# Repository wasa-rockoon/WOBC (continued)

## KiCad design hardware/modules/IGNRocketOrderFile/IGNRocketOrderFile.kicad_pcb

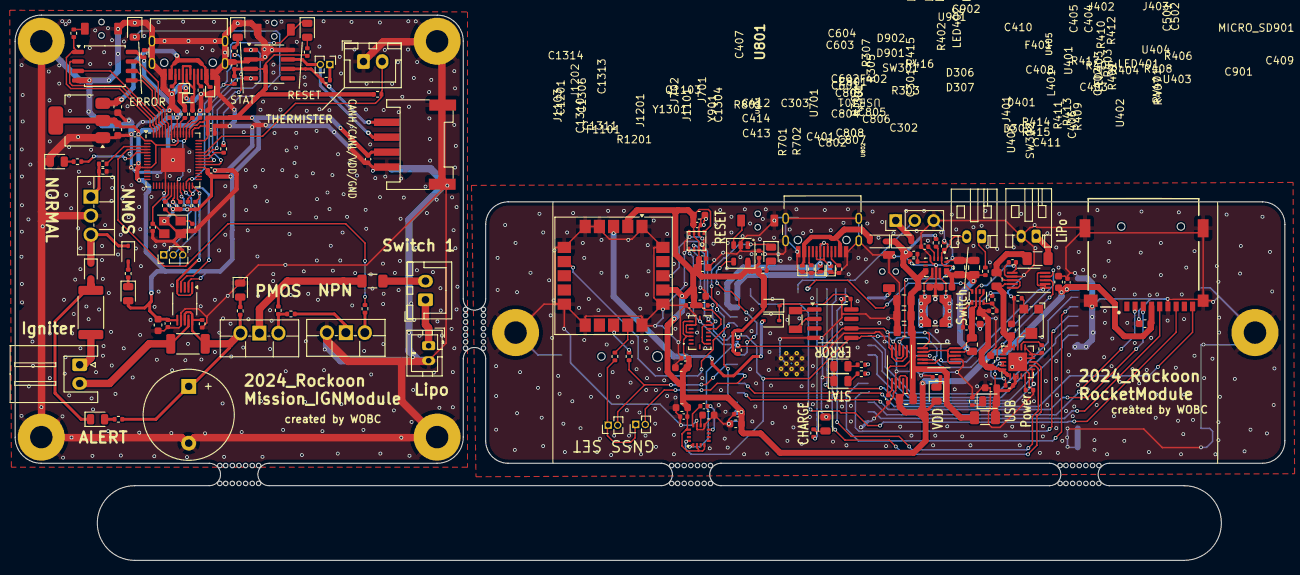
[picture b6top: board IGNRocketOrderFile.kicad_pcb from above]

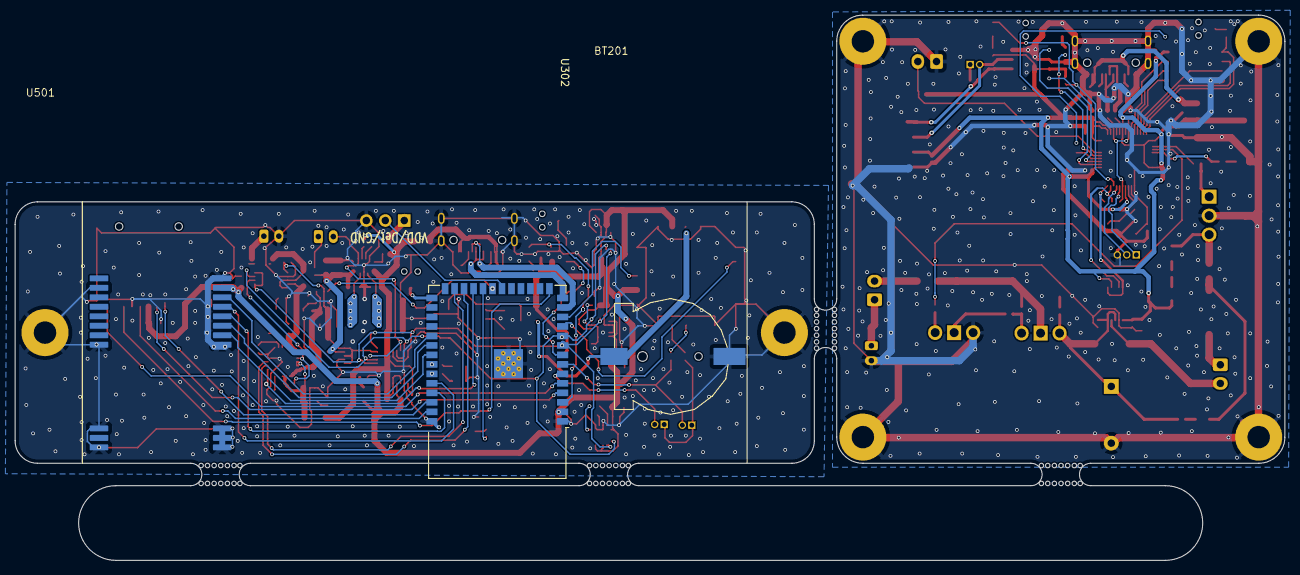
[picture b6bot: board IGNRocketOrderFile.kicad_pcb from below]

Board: 2 copper layers, 170.0 x 73.0 mm, 182 parts (3 on the bottom side), 126 nets.

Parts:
BT201: Battery_Cell; cr1220
BZ1101: Buzzer; Buzzer_12x9.5RM7.6
C301, C303, C403, C409, C410, C415, C502, C602, C603, C801, C802, C807, C902, C1102, C1201, C1301, C1302, C1305, C1306, C1308, C1310, C1311, C1312, C1313, C1314, C1315: 100nF; C_0402_1005Metric
C302, C401, C402, C406, C407, C408, C411, C501, C601, C604, C803, C804, C808, C901, C1001, C1002, C1101: 10uF; C_0603_1608Metric
C404, C405, C412, C413, C414: 22uF; C_0805_2012Metric
C805: 0.22uF; C_0402_1005Metric
C806: 4.7uF; C_0603_1608Metric
C1303, C1304: 27pF; C_0402_1005Metric
C1307, C1309: 1uF; C_0402_1005Metric
D301, D302, D304, D1302, D1303, D1304: 5V; D_SOD-882D
D303, D401, D901, D902: D; D_SOD-323
D305, D1301: RESET; LED_0805_2012Metric
D306, D1306: ERROR; LED_0805_2012Metric
D307, D1305: STAT; LED_0805_2012Metric
D1101: PMOS; LED_0805_2012Metric
D1102, D1104: D_Schottky; D_SOD-323
D1103: ALERT; LED_0805_2012Metric
D1105: NMOS; LED_0805_2012Metric
D1106: NORMAL; LED_0805_2012Metric
F401, F402, F1101: Polyfuse; Fuse_1206_3216Metric
J401: Conn_01x03; PinHeader_1x03_P2.54mm_Vertical
J402: Ext Switch; JST_PH_S2B-PH-K_1x02_P2.00mm_Horizontal
J403: LiPo; JST_PH_S2B-PH-K_1x02_P2.00mm_Horizontal
J701, J702: Conn_01x02; PinHeader_1x02_P1.27mm_Vertical
J1001: THERMISTER; JST_XH_B2B-XH-A_1x02_P2.50mm_Vertical
J1101: LiPo 1 Cell; JST_PH_B2B-PH-K_1x02_P2.00mm_Vertical
J1102: IGNITER; JST_XH_S2B-XH-A_1x02_P2.50mm_Horizontal
J1103: PowerSW; JST_XH_B2B-XH-A_1x02_P2.50mm_Vertical
J1201: Jumper; PinHeader_1x02_P1.27mm_Vertical
J1202: Conn_01x04_MountingPin; Grove_4P_L_SMD
J1301: DEBUG; PinHeader_1x03_P1.27mm_Vertical
L401: L; L_Wuerth_WE-TPC-3816
LED401: USB Power; LED_0805_2012Metric
LED402: CHARGE; LED_0805_2012Metric
LED403: VDD; LED_0805_2012Metric
MICRO_SD901: TF-01A
Q1101: Q_PMOS_GSD; TO-220F-3_Vertical
Q1102: Q_NMOS_GSD; TO-220F-3_Vertical
Q1103: Q_NPN_BEC; TO-220F-3_Vertical
R301, R302, R1303, R1304: 5.1k; R_0402_1005Metric
R303, R304, R306, R701, R702: 470; R_0402_1005Metric
R305, R307, R405, R406, R410, R1001, R1102, R1105, R1106, R1301, R1309, R1311: 10k; R_0402_1005Metric
R401, R402, R404, R417, R1101, R1108, R1110, R1111, R1112, R1302, R1305, R1308, R1310, R1312: 1k; R_0402_1005Metric
R403, R801: 4.7k; R_0402_1005Metric
R407, R408, R413: 100k; R_0402_1005Metric
R409, R412, R416: 50mΩ; R_0805_2012Metric
R411: 330k; R_0402_1005Metric
R414: 15k; R_0402_1005Metric
R415: 47k; R_0402_1005Metric
R1103: 20mΩ; R_2010_5025Metric
R1104: 1; R_2512_6332Metric
R1107, R1109: 510; R_0402_1005Metric
R1201: 120; R_0402_1005Metric
R1306, R1307: 22.4; R_0402_1005Metric
RV401: RV10k; Potentiometer_Bourns_TC33X_Vertical
SW301, SW1301: RESET_sw; TVAF06-A020B-R
SW302: Boot_sw; TVAF06-A020B-R
SW1302: BOOT0; TVAF06-A020B-R
U301: TPS3820; SOT-23-5
U302: ESP32-S3-WROOM-1
U401: TPS2116DRL; SOT-583-8
U402: MCP73871-1CC; QFN-20-1EP_4x4mm_P0.5mm_EP2.5x2.5mm
U403, U404, U406, U1101: INA226; VSSOP-10_3x3mm_P0.5mm
U405: TPS63070RNMR; VREG_TPS63070RNMR
U501: E220-900T22S(JP)
U601: BME280
U701: SAM-M10Q; ublox_SAM-M8Q
U801: BMI088
U802: QMC5883L; _HMC5883L
U901: PCF8563T; SOIC-8_3.9x4.9mm_P1.27mm
U1001: AMS1117-3.3; SOT-223-3_TabPin2
U1301: SN65HVD230; SOIC-8_3.9x4.9mm_P1.27mm
U1302: W25Q128JVS; SOIC-8_5.23x5.23mm_P1.27mm
U1303: RP2040; QFN-56-1EP_7x7mm_P0.4mm_EP3.2x3.2mm
USB301, USB1301: USB_C_Receptacle_USB2.0; USB_C_TYPEC-301S-ACP16X7
Y901: Crystal; Crystal_SMD_3215-2Pin_3.2x1.5mm
Y1301: Crystal_GND24; Crystal_SMD_3225-4Pin_3.2x2.5mm

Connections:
+BATT: BT201.1 (+), D901.2 (A), U701.3 (V_BCKP)
/IGN/HIGH: R1111.1, U1303.4 (GPIO2)
/IGN/I2C_SCL: R1311.2, U1101.1 (A1), U1101.5 (SCL), U1303.28 (GPIO17)
/IGN/I2C_SDA: R1309.2, U1101.4 (SDA), U1303.27 (GPIO16)
/IGN/IF/CANH: J1202.1, R1201.2, U1301.6 (CANL)
/IGN/IF/CANL: J1201.2, J1202.2, U1301.7 (CANH)
/IGN/LOW: R1109.1, U1303.3 (GPIO1)
/IGN/Normal: R1112.1, U1303.5 (GPIO3)
/IGN/RP2040core/CAN_RX: U1301.4 (R), U1303.35 (GPIO23)
/IGN/RP2040core/CAN_TX: U1301.1 (D), U1303.34 (GPIO22)
/IGN/RP2040core/GPIO26_ADC0: J1001.2, R1001.2, U1303.38 (GPIO26_ADC0)
/IGN/RP2040core/USB_D+: D1303.2 (A2), R1306.1, USB1301.A6 (D+), USB1301.B6 (D+)
/IGN/RP2040core/USB_D-: D1304.2 (A2), R1307.1, USB1301.A7 (D-), USB1301.B7 (D-)
/Rocket/AUX: U302.31 (GPIO38/FSPIWP/SUBSPIWP), U501.9 (AUX)
/Rocket/CHARGE: R402.2, U302.22 (GPIO14/TOUCH14/ADC2_CH3/FSPIWP/FSPIDQS/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)
/Rocket/CLK: MICRO_SD901.5 (CLK), U302.39 (GPIO1/TOUCH1/ADC1_CH0)
/Rocket/DetL: J401.2, U302.20 (GPIO12/TOUCH12/ADC2_CH1/FSPICLK/FSPIIO6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)
/Rocket/ESP32Core2/USB_D+: D302.2 (A2), U302.14 (GPIO20/U1CTS/ADC2_CH9/CLK_OUT1/USB_D+), USB301.A6 (D+), USB301.B6 (D+)
/Rocket/ESP32Core2/USB_D-: D304.2 (A2), U302.13 (GPIO19/U1RTS/ADC2_CH8/CLK_OUT2/USB_D-), USB301.A7 (D-), USB301.B7 (D-)
/Rocket/ESP32Core2/WDI: U301.4 (WDI), U302.8 (GPIO15/U0RTS/ADC2_CH4/XTAL_32K_P)
/Rocket/GPS_RESET: U302.12 (GPIO8/TOUCH8/ADC1_CH7/SUBSPICS1), U701.18 (~RESET)
/Rocket/I2C_SCL: R305.2, U302.9 (GPIO16/U0CTS/ADC2_CH5/XTAL_32K_N), U403.1 (A1), U403.5 (SCL), U404.1 (A1), U404.2 (A0), U404.5 (SCL), U406.1 (A1), U406.5 (SCL), U601.4 (SCK), U801.8 (SCL/SCK), U802.1 (SCL), U901.6 (SCL)
/Rocket/I2C_SDA: R307.2, U302.10 (GPIO17/U1TXD/ADC2_CH6), U403.4 (SDA), U404.4 (SDA), U406.2 (A0), U406.4 (SDA), U601.3 (SDI), U801.9 (SDA/SDI), U802.16 (SDA), U901.5 (SDA)
/Rocket/LiPoPower2/PROG: RV401.2, U402.13 (PROG1)
/Rocket/M0: U302.33 (MTDO/GPIO40/CLK_OUT2), U501.5 (M0)
/Rocket/M1: U302.32 (MTCK/GPIO39/CLK_OUT3/SUBSPICS1), U501.6 (M1)
/Rocket/MISO: MICRO_SD901.7 (DAT0), U302.15 (GPIO3/TOUCH3/ADC1_CH2)
/Rocket/MOSI: MICRO_SD901.3 (CMD), U302.4 (GPIO4/TOUCH4/ADC1_CH3)
/Rocket/PG: U302.23 (GPIO21), U402.6 (~PG)
/Rocket/RTX0: U302.36 (U0RXD/GPIO44/CLK_OUT2), U501.8 (TXD)
/Rocket/RTX1: J702.2, R702.2, U302.7 (GPIO7/TOUCH7/ADC1_CH6)
/Rocket/SD_DET: MICRO_SD901.CD1 (CD), U302.5 (GPIO5/TOUCH5/ADC1_CH4)
/Rocket/SS: MICRO_SD901.2 (CD/DAT3), U302.38 (GPIO2/TOUCH2/ADC1_CH1)
/Rocket/ST: U302.21 (GPIO13/TOUCH13/ADC2_CH2/FSPIQ/FSPIIO7/S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), U401.8 (ST)
/Rocket/STAT1: U302.24 (GPIO47/SPICLK_P/SUBSPICLK_P_DIFF), U402.8 (STAT1/~LBO)
/Rocket/STAT2: U302.25 (GPIO48/SPICLK_N/SUBSPICLK_N_DIFF), U402.7 (STAT2)
/Rocket/TRX0: U302.37 (U0TXD/GPIO43/CLK_OUT1), U501.7 (RXD)
/Rocket/TRX1: J701.2, U302.6 (GPIO6/TOUCH6/ADC1_CH5)
/Rocket/TimePulse: U302.11 (GPIO18/U1RXD/ADC2_CH7/CLK_OUT3), U701.7 (TIMEPULSE)
GND: BT201.2 (-), BZ1101.2 (-), C301.1, C302.1, C303.2, C401.2, C402.2, C403.2, C404.2, C405.2, C406.2, C407.2, C408.2, C409.2, C410.2, C411.2, C412.2, C413.2, C414.2, C415.2, C501.2, C502.2, C601.2, C602.2, C603.2, C604.2, C801.2, C802.2, C803.2, C804.2, C806.2, C807.2, C808.2, C901.2, C902.1, C1001.2, C1002.2, C1101.2, C1102.2, C1201.1, C1301.1, C1302.1, C1303.1, C1304.1, C1305.2, C1306.2, C1307.1, C1308.2, C1309.1, C1310.2, C1311.2, C1312.2, C1313.2, C1314.2, C1315.2, D301.1 (A1), D302.1 (A1), D304.1 (A1), D306.1 (K), D307.1 (K), D1101.1 (K), D1106.1 (K), D1302.1 (A1), D1303.1 (A1), D1304.1 (A1), D1305.1 (K), D1306.1 (K), J401.3, J403.2, J1001.1, J1101.2, J1202.4, J1202.MP (MountPin), J1301.3, LED402.1 (K), MICRO_SD901.6 (VSS), MICRO_SD901.MP1 (SHIELD), MICRO_SD901.MP2 (SHIELD), MICRO_SD901.MP3 (SHIELD), MICRO_SD901.MP4 (SHIELD), Q1102.3 (D), Q1103.3 (E), R301.2, R302.2, R401.2, R403.1, R404.2, R406.2, R407.2, R411.2, R414.1, R417.2, R1102.1, R1106.1, R1303.2, R1304.2, SW301.2, SW302.2, SW1301.2, SW1302.1, U301.2 (GND), U302.1 (GND), U302.40 (GND), U302.41 (GND), U401.1 (GND), U402.9 (~TE), U402.10 (V_{SS}), U402.11 (V_{SS}), U402.21 (V_{SS}), U403.7 (GND), U404.7 (GND), U405.4 (GND), U405.10 (PGND), U405.15 (VSEL), U406.7 (GND), U501.1 (GND), U501.2 (GND), U501.3 (GND), U501.4 (GND), U501.11 (GND), U501.13 (GND), U501.19 (GND), U501.20 (GND), U501.22 (GND), U601.1 (GND), U601.5 (SDO), U601.7 (GND), U701.1 (GND), U701.4 (GND), U701.5 (GND), U701.6 (GND), U701.10 (GND), U701.11 (GND), U701.15 (GND), U701.16 (GND), U701.20 (GND), U801.4 (GNDA), U801.6 (GNDIO), U802.9 (GND), U802.11 (GND), U901.4 (VSS), U1001.1 (GND), U1101.7 (GND), U1301.2 (GND), U1301.8 (Rs), U1302.4 (GND), U1303.19 (TESTEN), U1303.57 (GND), USB301.A1 (GND), USB301.A12 (GND), USB301.B1 (GND), USB301.B12 (GND), USB301.S1 (SHIELD), USB1301.A1 (GND), USB1301.A12 (GND), USB1301.B1 (GND), USB1301.B12 (GND), USB1301.S1 (SHIELD), Y1301.2, Y1301.4
unnamed: BZ1101.1 (+), Q1101.3 (S), R1101.1, R1102.2, R1103.2, R1108.1, U1101.8 (Vbus), U1101.10 (Vin+)
unnamed: C1304.2, R1308.1, Y1301.1
unnamed: D301.2 (A2), D303.2 (A), USB301.A4 (VBUS), USB301.A9 (VBUS), USB301.B4 (VBUS), USB301.B9 (VBUS)
unnamed: D305.2 (A), R303.2
unnamed: D306.2 (A), R304.2
unnamed: D307.2 (A), R306.2
unnamed: D401.2 (A), J401.1
unnamed: C902.2, D901.1 (K), D902.1 (K), U901.8 (VDD)
unnamed: D1101.2 (A), R1101.2
unnamed: D1102.2 (A), D1103.1 (K), R1104.2
unnamed: D1102.1 (K), D1104.1 (K), Q1102.2 (S)
unnamed: D1103.2 (A), R1108.2
unnamed: D1104.2 (A), R1110.2
unnamed: D1105.1 (K), R1110.1
unnamed: D1106.2 (A), R1112.2
unnamed: D1301.2 (A), R1302.2
unnamed: D1305.2 (A), R1310.2
unnamed: D1306.2 (A), R1312.2
unnamed: J402.1, R410.1
unnamed: J402.2, R411.1, U403.3 (~Alert), U405.1 (PS/SYNC), U405.14 (EN), U406.3 (~Alert)
unnamed: F402.2, J403.1
unnamed: J701.1, J702.1, R701.2
unnamed: J1101.1, J1103.1
unnamed: J1102.1, R1104.1
unnamed: J1102.2, R1103.1, U1101.9 (Vin-)
unnamed: F1101.1, J1103.2
unnamed: J1201.1, R1201.1
unnamed: J1301.1, U1303.24 (SWCLK)
unnamed: J1301.2, U1303.25 (SWD)
unnamed: C401.1, F401.2, LED401.2 (A), R408.1, U402.2 (VPCC), U402.3 (SEL), U402.18 (IN), U402.19 (IN)
unnamed: LED401.1 (K), R401.1
unnamed: LED402.2 (A), R402.1
unnamed: LED403.1 (K), R417.1
unnamed: F1101.2, Q1101.1 (D), R1105.1
unnamed: Q1101.2 (G), R1105.2, R1107.1
unnamed: Q1102.1 (G), R1106.2, R1109.2
unnamed: Q1103.2 (B), R1111.2
unnamed: Q1103.1 (C), R1107.2
unnamed: R404.1, RV401.3
unnamed: R1305.2, SW1302.2
unnamed: SW301.1, U301.3 (MR)
unnamed: SW302.1, U302.27 (GPIO0/BOOT)
unnamed: R304.1, U302.34 (MTDI/GPIO41/CLK_OUT1)
unnamed: R306.1, U302.35 (MTMS/GPIO42)
unnamed: C402.1, C406.1, R405.1, U401.3 (VIN1), U401.5 (MODE), U402.1 (OUT), U402.20 (OUT)
unnamed: R403.2, R405.2, U401.4 (PR1)
unnamed: R408.2, U402.17 (CE), U404.3 (~Alert)
unnamed: R407.1, U402.12 (PROG3)
unnamed: R406.1, U402.5 (THERM)
unnamed: C407.1, R412.1, U402.14 (V_{BAT}), U402.15 (V_{BAT}), U402.16 (V_{BAT_SENSE}), U404.9 (Vin-)
unnamed: C404.1, C405.1, C408.1, R409.2, R410.2, U403.9 (Vin-), U405.12_13 (VIN)
unnamed: F402.1, R412.2, U404.8 (Vbus), U404.10 (Vin+)
unnamed: R414.2, R415.1, U405.5 (FB)
unnamed: L401.1, U405.11 (L1)
unnamed: L401.2, U405.9 (L2)
unnamed: R413.2, U405.2 (PG)
unnamed: C410.1, U405.3 (VAUX)
unnamed: R701.1, U701.14 (RXD)
unnamed: R702.1, U701.13 (TXD)
unnamed: R801.1, U801.10 (SDO2), U801.15 (SDO1)
unnamed: C806.1, U802.10 (C1)
unnamed: C805.1, U802.12 (SETC)
unnamed: C805.2, U802.8 (STEP)
unnamed: U901.1 (OSCI), Y901.1
unnamed: U901.2 (OSCO), Y901.2
unnamed: U1302.6 (CLK), U1303.52 (QSPI_SCLK)
unnamed: U1302.5 (DI(IO0)), U1303.53 (QSPI_SD0)
unnamed: U1302.2 (DO(IO1)), U1303.55 (QSPI_SD1)
unnamed: U1302.3 (IO2), U1303.54 (QSPI_SD2)
unnamed: U1302.7 (IO3), U1303.51 (QSPI_SD3)
unnamed: R1305.1, U1302.1 (~CS), U1303.56 (QSPI_SS)
unnamed: R1312.1, U1303.36 (GPIO24)
unnamed: R1310.1, U1303.37 (GPIO25)
unnamed: R1307.2, U1303.46 (USB_DM)
unnamed: R1306.2, U1303.47 (USB_DP)
unnamed: C1305.1, C1306.1, C1307.2, U1303.23 (DVDD), U1303.45 (VREG_VOUT), U1303.50 (DVDD)
unnamed: C1303.2, U1303.20 (XIN), Y1301.3
unnamed: R1308.2, U1303.21 (XOUT)
unnamed: R301.1, USB301.A5 (CC1)
unnamed: R302.1, USB301.B5 (CC2)
unnamed: R1303.1, USB1301.A5 (CC1)
unnamed: R1304.1, USB1301.B5 (CC2)
RESET: D305.1 (K), D1301.1 (K), R1301.2, SW1301.1, U301.1 (RESET), U302.3 (EN), U1303.26 (RUN)
VBUS: C411.1, C412.1, C413.1, C414.1, C415.1, C1001.1, D303.1 (K), D401.1 (K), D1302.2 (A2), F401.1, R413.1, R415.2, R416.1, U405.7_8 (VOUT), U406.6 (VS), U406.8 (Vbus), U406.10 (Vin+), U1001.3 (VI), USB1301.A4 (VBUS), USB1301.A9 (VBUS), USB1301.B4 (VBUS), USB1301.B9 (VBUS)
VDD: C301.2, C302.2, C303.1, C501.1, C502.1, C601.1, C602.1, C603.1, C604.1, C801.1, C802.1, C803.1, C804.1, C807.1, C808.1, C901.1, C1002.1, C1101.1, C1102.1, C1201.2, C1301.2, C1302.2, C1308.1, C1309.2, C1310.1, C1311.1, C1312.1, C1313.1, C1314.1, C1315.1, D902.2 (A), D1105.2 (A), J1202.3, LED403.2 (A), MICRO_SD901.4 (VDD), R303.1, R305.1, R307.1, R416.2, R801.2, R1001.1, R1301.1, R1302.1, R1309.1, R1311.1, U301.5 (VDD), U302.2 (3V3), U406.9 (Vin-), U501.10 (VDD), U601.2 (CSB), U601.6 (VDDIO), U601.8 (VDD), U701.2 (VCC_IO), U701.17 (VCC), U801.3 (VDD), U801.7 (PS), U801.11 (VDDIO), U802.2 (VDD), U802.4 (S1), U802.13 (VDDIO), U1001.2 (VO), U1101.2 (A0), U1101.6 (VS), U1301.3 (VCC), U1302.8 (VCC), U1303.1 (IOVDD), U1303.10 (IOVDD), U1303.22 (IOVDD), U1303.33 (IOVDD), U1303.42 (IOVDD), U1303.43 (ADC_AVDD), U1303.44 (VREG_IN), U1303.48 (USB_VDD), U1303.49 (IOVDD)
VPP: C403.1, C409.1, R409.1, U401.2 (VOUT), U401.7 (VOUT), U403.2 (A0), U403.6 (VS), U403.8 (Vbus), U403.10 (Vin+), U404.6 (VS)

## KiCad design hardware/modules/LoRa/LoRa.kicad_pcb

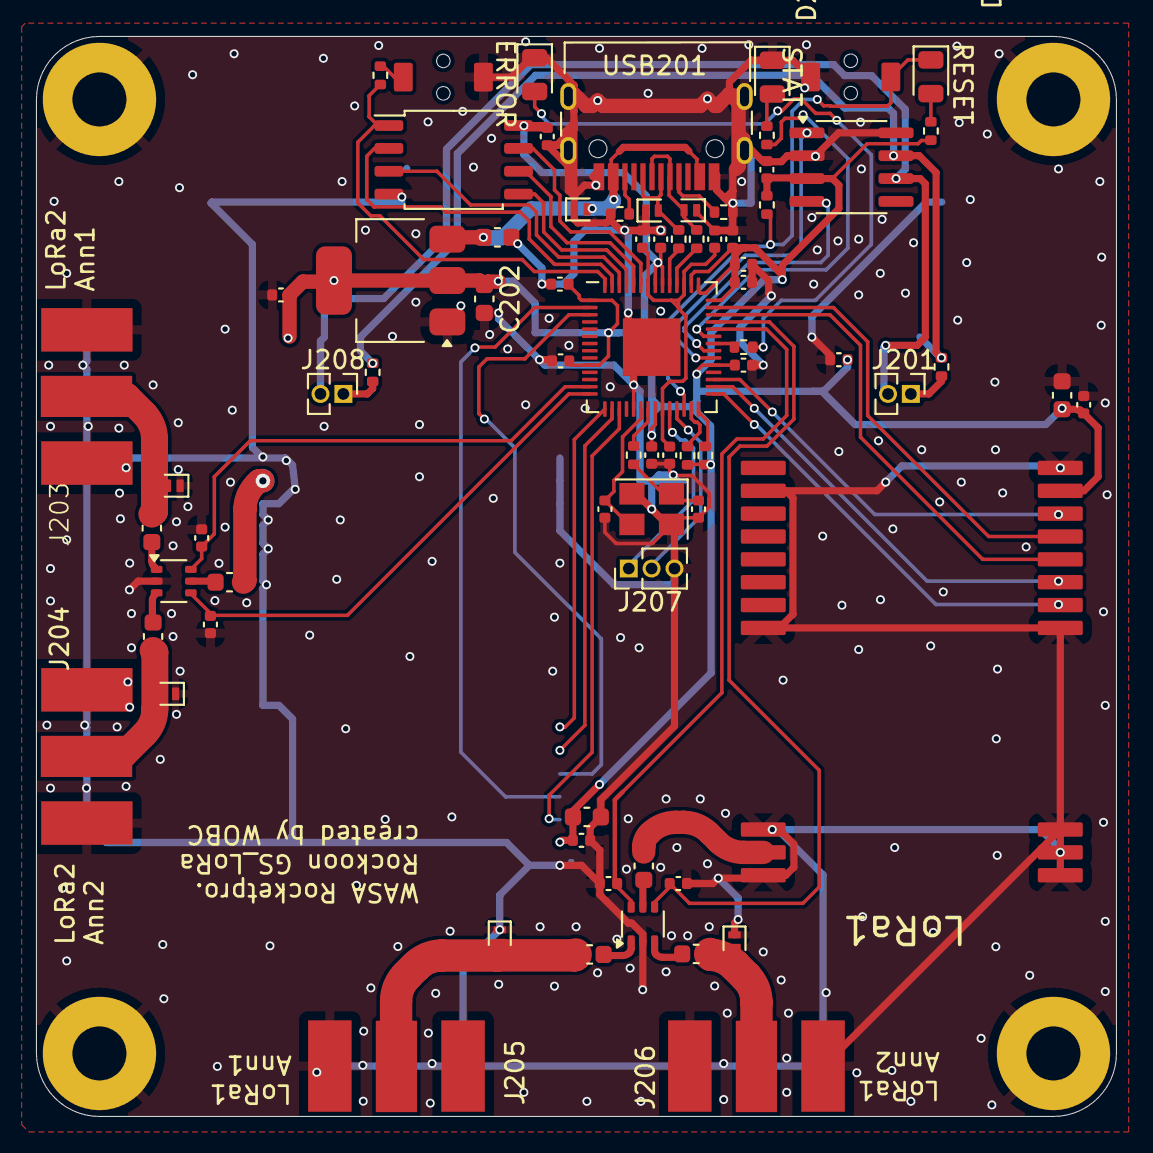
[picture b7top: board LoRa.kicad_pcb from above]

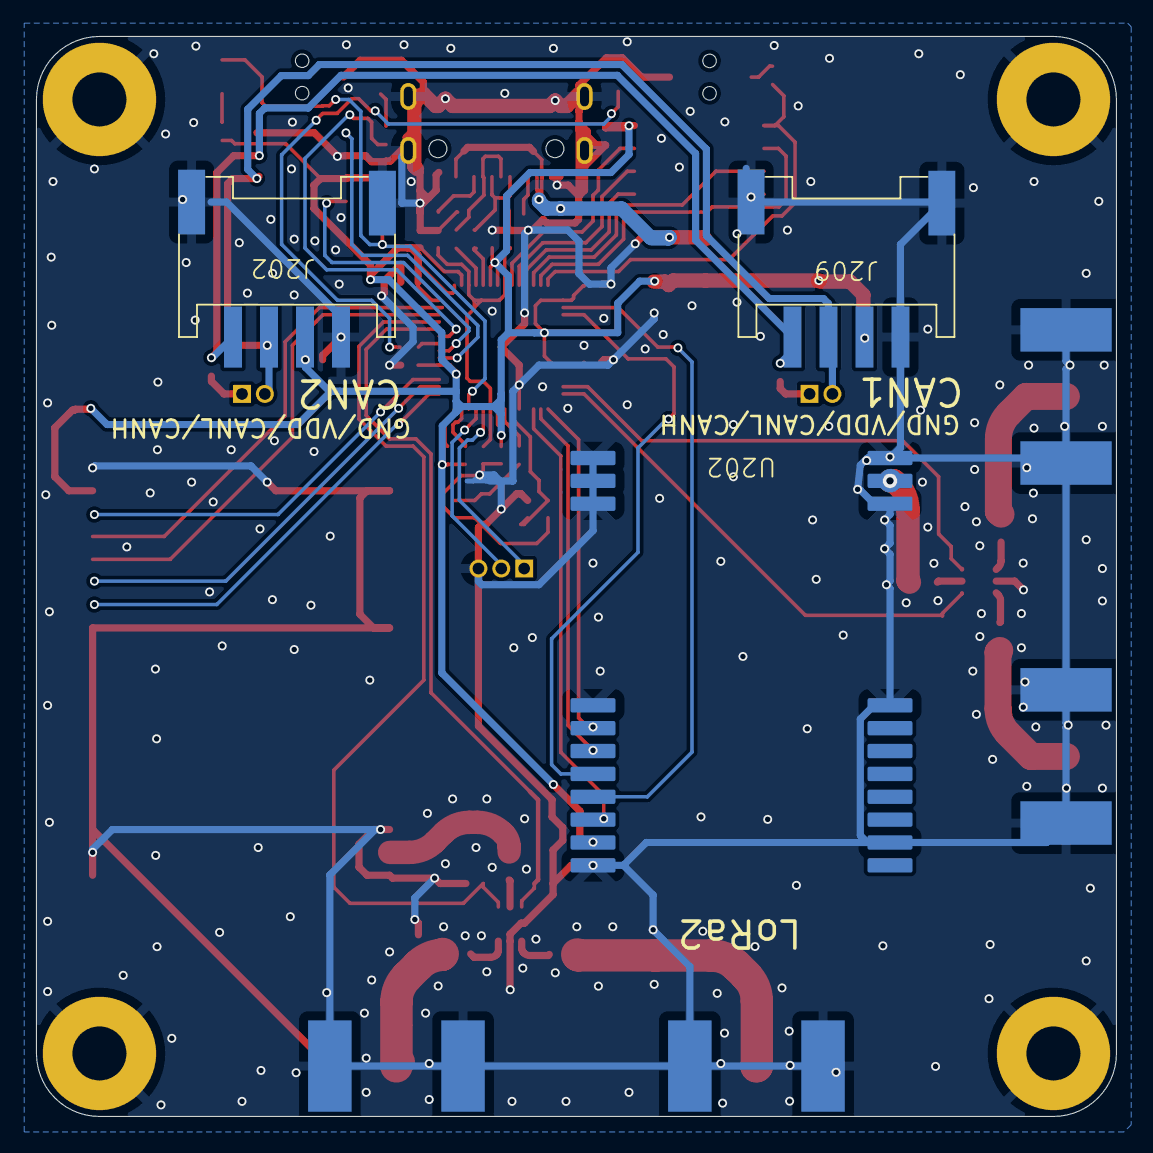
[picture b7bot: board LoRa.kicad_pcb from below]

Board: 2 copper layers, 60.0 x 60.0 mm, 78 parts (3 on the bottom side), 62 nets.

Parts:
C201, C202, C209, C216: 10u; C_0603_1608Metric
C203, C218, C219, C222, C223, C225, C227, C228, C229, C230, C231, C232, C233: 100nF; C_0402_1005Metric
C204, C205, C208, C211, C212, C215: 100p; C_0603_1608Metric
C206, C207, C210, C213, C214, C217: 100n; C_0402_1005Metric
C220, C221: 27pF; C_0402_1005Metric
C224, C226: 1uF; C_0402_1005Metric
D201, D202, D203, D204: ESD9B5.0ST5G; D_SOD-882
D205: RESET; LED_0805_2012Metric
D206, D207, D208: 5V; D_SOD-882
D209: STAT; LED_0805_2012Metric
D210: ERROR; LED_0805_2012Metric
J201, J208: Jumper; PinHeader_1x02_P1.27mm_Vertical
J202, J209: Conn_01x04_MountingPin; Grove_4P_L_SMD
J203, J204, J205, J206: SMA; SMA_aki
J207: DEBUG; PinHeader_1x03_P1.27mm_Vertical
R201, R214: 120; R_0402_1005Metric
R202, R210, R212: 10k; R_0402_1005Metric
R203, R206, R209, R211, R213: 1k; R_0402_1005Metric
R204, R205: 22k; R_0402_1005Metric
R207, R208: 22.4; R_0402_1005Metric
SW201: RESET_sw; TVAF06-A020B-R
SW202: BOOT0; TVAF06-A020B-R
Switch201, Switch202: XA17-G4K1; SOT-363_SC-70-6
U201: AMS1117-3.3; SOT-223-3_TabPin2
U202, U203: E220-900T22S(JP)
U204: SN65HVD230; SOIC-8_3.9x4.9mm_P1.27mm
U205: W25Q128JVS; SOIC-8_5.23x5.23mm_P1.27mm
U206: RP2040; QFN-56-1EP_7x7mm_P0.4mm_EP3.2x3.2mm
USB201: USB_C_Receptacle_USB2.0; USB_C_TYPEC-301S-ACP16X7
Y201: Crystal_GND24; Crystal_SMD_3225-4Pin_3.2x2.5mm

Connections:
/IF3/CANH: J202.1, J209.1, R201.2, R214.2, U204.7 (CANH)
/IF3/CANL: J201.2, J202.2, J208.2, J209.2, U204.6 (CANL)
/LoRa1/LoRa_RTX: U202.8 (TXD), U206.2 (GPIO0)
/LoRa1/LoRa_TRX: U202.7 (RXD), U206.3 (GPIO1)
/LoRa2/LoRa_RTX: U203.8 (TXD), U206.41 (GPIO29_ADC3)
/LoRa2/LoRa_TRX: U203.7 (RXD), U206.40 (GPIO28_ADC2)
/PR2040_2/CAN_RX: U204.4 (R), U206.35 (GPIO23)
/PR2040_2/CAN_TX: U204.1 (D), U206.34 (GPIO22)
/PR2040_2/I2C_SCL: R212.2, U206.28 (GPIO17)
/PR2040_2/I2C_SDA: R210.2, U206.27 (GPIO16)
/PR2040_2/USB_D+: D207.2 (A2), R207.1, USB201.A6 (D+), USB201.B6 (D+)
/PR2040_2/USB_D-: D208.2 (A2), R208.1, USB201.A7 (D-), USB201.B7 (D-)
/RF1AUX: U202.9 (AUX), U206.17 (GPIO14)
/RF1M0: U202.5 (M0), U206.15 (GPIO12)
/RF1M1: U202.6 (M1), U206.16 (GPIO13)
/RF1sw1: C206.1, Switch201.6 (V2), U206.13 (GPIO10)
/RF1sw2: C207.1, Switch201.4 (V1), U206.14 (GPIO11)
/RF2AUX: U203.9 (AUX), U206.31 (GPIO20)
/RF2M0: U203.5 (M0), U206.29 (GPIO18)
/RF2M1: U203.6 (M1), U206.30 (GPIO19)
/RF2sw1: C213.1, Switch202.6 (V2), U206.38 (GPIO26_ADC0)
/RF2sw2: C214.1, Switch202.4 (V1), U206.39 (GPIO27_ADC1)
GND: C201.2, C202.2, C203.1, C206.2, C207.2, C209.2, C210.2, C213.2, C214.2, C216.2, C217.2, C218.1, C219.1, C220.1, C221.1, C222.2, C223.2, C224.1, C225.2, C226.1, C227.2, C228.2, C229.2, C230.2, C231.2, C232.2, C233.1, D201.1 (A1), D202.1 (A1), D203.1 (A1), D204.1 (A1), D206.1 (A1), D207.1 (A1), D208.1 (A1), D209.1 (K), D210.1 (K), J202.4, J202.MP (MountPin), J203.2 (Ext), J204.2 (Ext), J205.2 (Ext), J206.2 (Ext), J207.3, J209.4, J209.MP (MountPin), R204.2, R205.2, SW201.2, SW202.1, Switch201.2 (GND), Switch202.2 (GND), U201.1 (GND), U202.1 (GND), U202.2 (GND), U202.3 (GND), U202.4 (GND), U202.11 (GND), U202.13 (GND), U202.19 (GND), U202.20 (GND), U202.22 (GND), U203.1 (GND), U203.2 (GND), U203.3 (GND), U203.4 (GND), U203.11 (GND), U203.13 (GND), U203.19 (GND), U203.20 (GND), U203.22 (GND), U204.2 (GND), U204.8 (Rs), U205.4 (GND), U206.19 (TESTEN), U206.57 (GND), USB201.A1 (GND), USB201.A12 (GND), USB201.B1 (GND), USB201.B12 (GND), USB201.S1 (SHIELD), Y201.2, Y201.4
unnamed: C221.2, R209.1, Y201.1
unnamed: C204.2, D201.2 (A2), J203.1 (In)
unnamed: C205.2, D202.2 (A2), J204.1 (In)
unnamed: C211.2, D203.2 (A2), J205.1 (In)
unnamed: C212.2, D204.2 (A2), J206.1 (In)
unnamed: D205.2 (A), R203.2
unnamed: D209.2 (A), R211.2
unnamed: D210.2 (A), R213.2
unnamed: J201.1, R201.1
unnamed: J207.1, U206.24 (SWCLK)
unnamed: J207.2, U206.25 (SWD)
unnamed: J208.1, R214.1
unnamed: R206.2, SW202.2
unnamed: C208.2, Switch201.5 (J1)
unnamed: C205.1, Switch201.3 (J2)
unnamed: C204.1, Switch201.1 (J3)
unnamed: C215.2, Switch202.5 (J1)
unnamed: C212.1, Switch202.3 (J2)
unnamed: C211.1, Switch202.1 (J3)
unnamed: C208.1, U202.21 (ANT)
unnamed: C215.1, U203.21 (ANT)
unnamed: U205.6 (CLK), U206.52 (QSPI_SCLK)
unnamed: U205.5 (DI(IO0)), U206.53 (QSPI_SD0)
unnamed: U205.2 (DO(IO1)), U206.55 (QSPI_SD1)
unnamed: U205.3 (IO2), U206.54 (QSPI_SD2)
unnamed: U205.7 (IO3), U206.51 (QSPI_SD3)
unnamed: R206.1, U205.1 (~CS), U206.56 (QSPI_SS)
unnamed: R213.1, U206.36 (GPIO24)
unnamed: R211.1, U206.37 (GPIO25)
unnamed: R208.2, U206.46 (USB_DM)
unnamed: R207.2, U206.47 (USB_DP)
unnamed: C222.1, C223.1, C224.2, U206.23 (DVDD), U206.45 (VREG_VOUT), U206.50 (DVDD)
unnamed: C220.2, U206.20 (XIN), Y201.3
unnamed: R209.2, U206.21 (XOUT)
unnamed: R204.1, USB201.A5 (CC1)
unnamed: R205.1, USB201.B5 (CC2)
RESET: D205.1 (K), R202.2, SW201.1, U206.26 (RUN)
VBUS: C201.1, D206.2 (A2), U201.3 (VI), USB201.A4 (VBUS), USB201.A9 (VBUS), USB201.B4 (VBUS), USB201.B9 (VBUS)
VDD: C202.1, C203.2, C209.1, C210.1, C216.1, C217.1, C218.2, C219.2, C225.1, C226.2, C227.1, C228.1, C229.1, C230.1, C231.1, C232.1, C233.2, J202.3, J209.3, R202.1, R203.1, R210.1, R212.1, U201.2 (VO), U202.10 (VDD), U203.10 (VDD), U204.3 (VCC), U205.8 (VCC), U206.1 (IOVDD), U206.10 (IOVDD), U206.22 (IOVDD), U206.33 (IOVDD), U206.42 (IOVDD), U206.43 (ADC_AVDD), U206.44 (VREG_IN), U206.48 (USB_VDD), U206.49 (IOVDD)
